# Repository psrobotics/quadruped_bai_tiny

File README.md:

# Quadruped_bai_tiny v1

Still working on detailed document.

## Videos

[Walking](https://youtu.be/wHSh3s8Uc68)  /  [Jumping](https://youtu.be/LqSfARLMR58)  /  [Leg demo](https://www.youtube.com/watch?v=xufyeLivXR8)

## File Structure

* /hardware - CAD design

* /electronic - Motor driver, Main controller brd, Encoder brd, IIC bridge brd

* /sim - V-rep simulation, Kinematics, Dynamics

* /software - Firmware

## Reducer

## Leg Assembly

## Body Assembly

## Motor Driver

## Main Controller

## License
MIT License

## Contact
* Shuang Peng, {shuangpe}@usc.edu

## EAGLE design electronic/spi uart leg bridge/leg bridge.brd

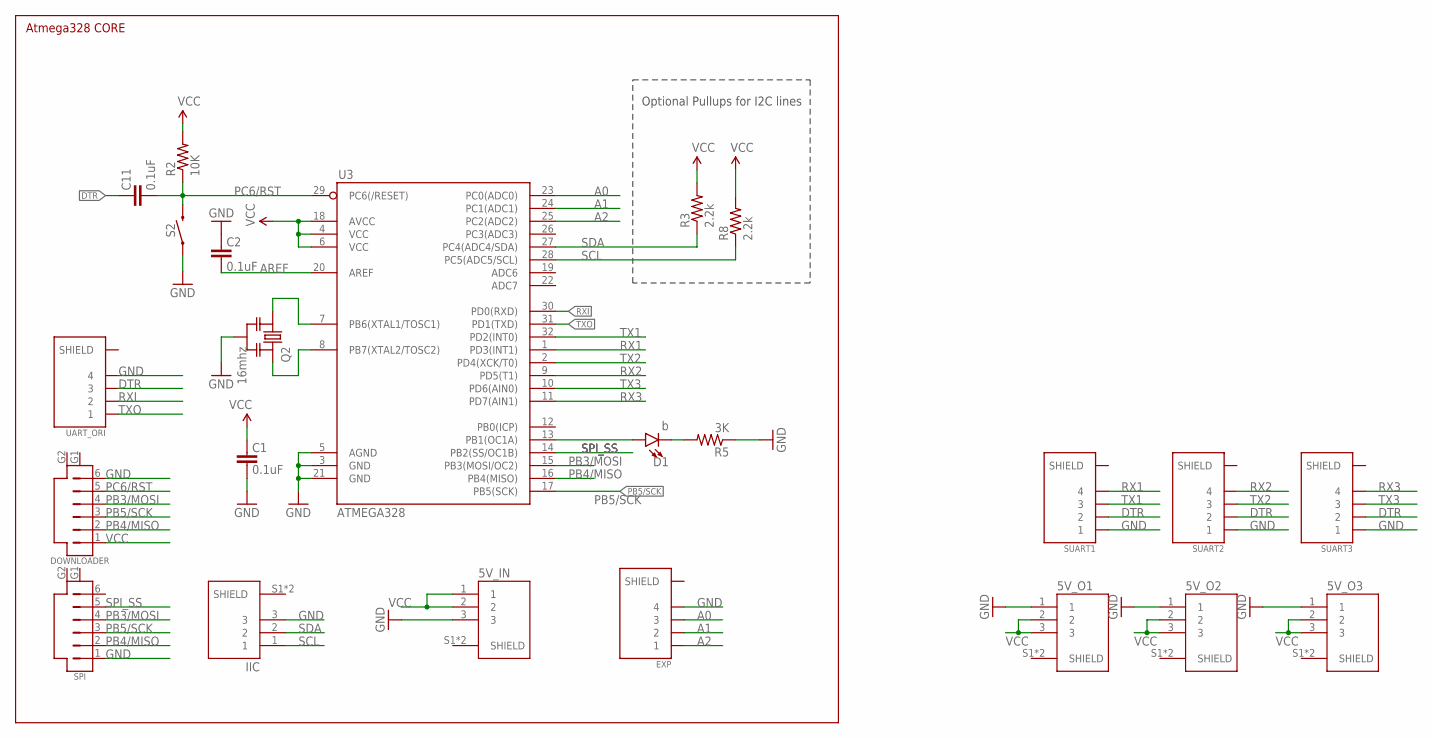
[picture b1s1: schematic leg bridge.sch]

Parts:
5V_IN, 5V_O1, 5V_O2, 5V_O3: SM03B-SRSS-TB(LF)(SN); JST_SM03B-SRSS-TB(LF)(SN)
C1, C2, C11: 0.1uF; 0603-CAP
D1: b; LED-0603
DOWNLOADER: SM06B-SRSS-TB; SM06B
EXP: SM04B-SRSS-TB(LF)(SN); JST_SM04B-SRSS-TB(LF)(SN)
IIC: SM03B-SRSS-TB(LF)(SN); JST_SM03B-SRSS-TB(LF)(SN)
Q2: 16mhz; RESONATOR_MURATA2
R2: 10K; 0603-RES
R3, R8: 2.2k; 0603-RES
R5: 3K; 0603-RES
S2: MOMENTARY-SWITCH-SPST-SMD-RIGHT-ANGLE; TACTILE_SWITCH_SMD_RIGHT_ANGLE
SPI: SM06B-SRSS-TB; SM06B
SUART1, SUART2, SUART3: SM04B-SRSS-TB(LF)(SN); JST_SM04B-SRSS-TB(LF)(SN)
U3: ATMEGA328; TQFP32-08
UART_ORI: SM04B-SRSS-TB(LF)(SN); JST_SM04B-SRSS-TB(LF)(SN)

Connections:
A0: EXP.3, U3.23 (PC0(ADC0))
A1: EXP.2, U3.24 (PC1(ADC1))
A2: EXP.1, U3.25 (PC2(ADC2))
AREF: C2.1, U3.20 (AREF)
DTR: C11.2, SUART1.2, SUART2.2, SUART3.2, UART_ORI.3
GND: 5V_IN.3, 5V_O1.1, 5V_O2.1, 5V_O3.1, C1.1, C2.2, DOWNLOADER.6, EXP.4, IIC.3, Q2.2, R5.1, S2.1, SPI.1, SUART1.1, SUART2.1, SUART3.1, U3.3 (GND), U3.5 (AGND), U3.21 (GND), UART_ORI.4
unnamed: Q2.1, U3.7 (PB6(XTAL1/TOSC1))
unnamed: Q2.3, U3.8 (PB7(XTAL2/TOSC2))
unnamed: D1.A, U3.13 (PB1(OC1A))
unnamed: D1.C, R5.2
PB3/MOSI: DOWNLOADER.4, SPI.4, U3.15 (PB3(MOSI/OC2))
PB4/MISO: DOWNLOADER.2, SPI.2, U3.16 (PB4(MISO))
PB5/SCK: DOWNLOADER.3, SPI.3, U3.17 (PB5(SCK))
PC6/RST: C11.1, DOWNLOADER.5, R2.1, S2.2, U3.29 (PC6(/RESET))
RX1: SUART1.4, U3.1 (PD3(INT1))
RX2: SUART2.4, U3.9 (PD5(T1))
RX3: SUART3.4, U3.11 (PD7(AIN1))
RXI: U3.30 (PD0(RXD)), UART_ORI.2
SCL: IIC.1, R8.1, U3.28 (PC5(ADC5/SCL))
SDA: IIC.2, R3.1, U3.27 (PC4(ADC4/SDA))
SPI_SS: SPI.5, U3.14 (PB2(SS/OC1B))
TX1: SUART1.3, U3.32 (PD2(INT0))
TX2: SUART2.3, U3.2 (PD4(XCK/T0))
TX3: SUART3.3, U3.10 (PD6(AIN0))
TXO: U3.31 (PD1(TXD)), UART_ORI.1
VCC: 5V_IN.1, 5V_IN.2, 5V_O1.2, 5V_O1.3, 5V_O2.2, 5V_O2.3, 5V_O3.2, 5V_O3.3, C1.2, DOWNLOADER.1, R2.2, R3.2, R8.2, U3.4 (VCC), U3.6 (VCC), U3.18 (AVCC)

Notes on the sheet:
Optional Pullups for I2C lines
Atmega328 CORE

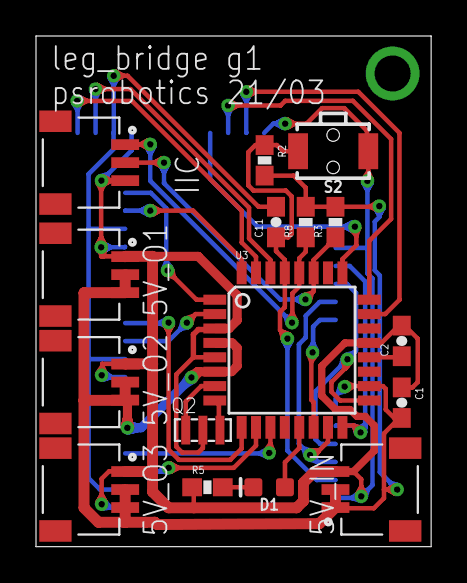
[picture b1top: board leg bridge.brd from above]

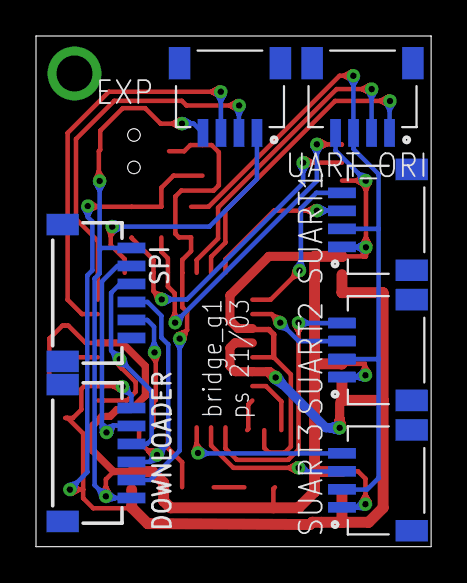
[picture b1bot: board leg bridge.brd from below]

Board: 2 copper layers, 22.0 x 28.4 mm, 23 parts (7 on the bottom side), 26 nets.

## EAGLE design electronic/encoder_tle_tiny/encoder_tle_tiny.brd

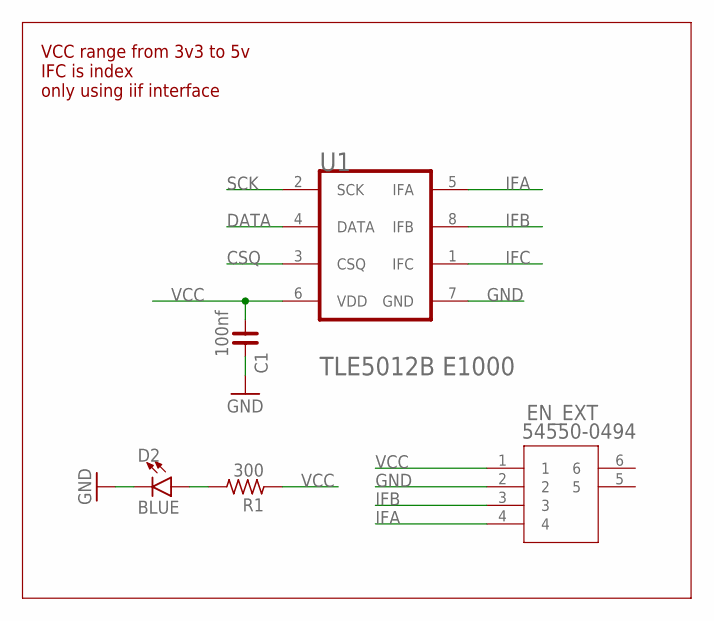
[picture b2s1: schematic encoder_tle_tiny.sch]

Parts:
C1: 100nf; C0603
D2: BLUE; LED-0603
EN_EXT: 54550-0494; CON4_1X4_DRB2_MOL
R1: 300; R0603
U1: INFINEON_TLE5012B_E1000INFINEON_TLE5012B_E1000_0_1; INFINEON_TLE5012B_E1000_1

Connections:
CSQ: U1.3 (CSQ)
DATA: U1.4 (DATA)
GND: C1.2, D2.C, EN_EXT.2, U1.7 (GND)
IFA: EN_EXT.4, U1.5 (IFA)
IFB: EN_EXT.3, U1.8 (IFB)
IFC: U1.1 (IFC)
unnamed: D2.A, R1.2
SCK: U1.2 (SCK)
VCC: C1.1, EN_EXT.1, R1.1, U1.6 (VDD)

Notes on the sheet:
VCC range from 3v3 to 5v IFC is index only using iif interface

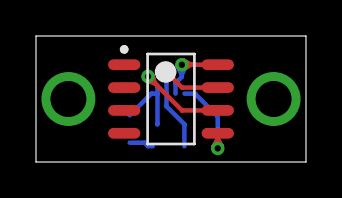
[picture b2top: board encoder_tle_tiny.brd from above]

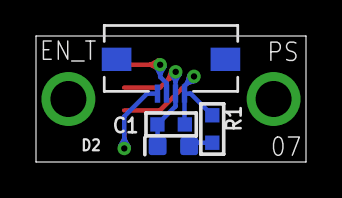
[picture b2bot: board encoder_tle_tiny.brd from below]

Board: 2 copper layers, 15.0 x 7.0 mm, 5 parts (4 on the bottom side), 5 nets.

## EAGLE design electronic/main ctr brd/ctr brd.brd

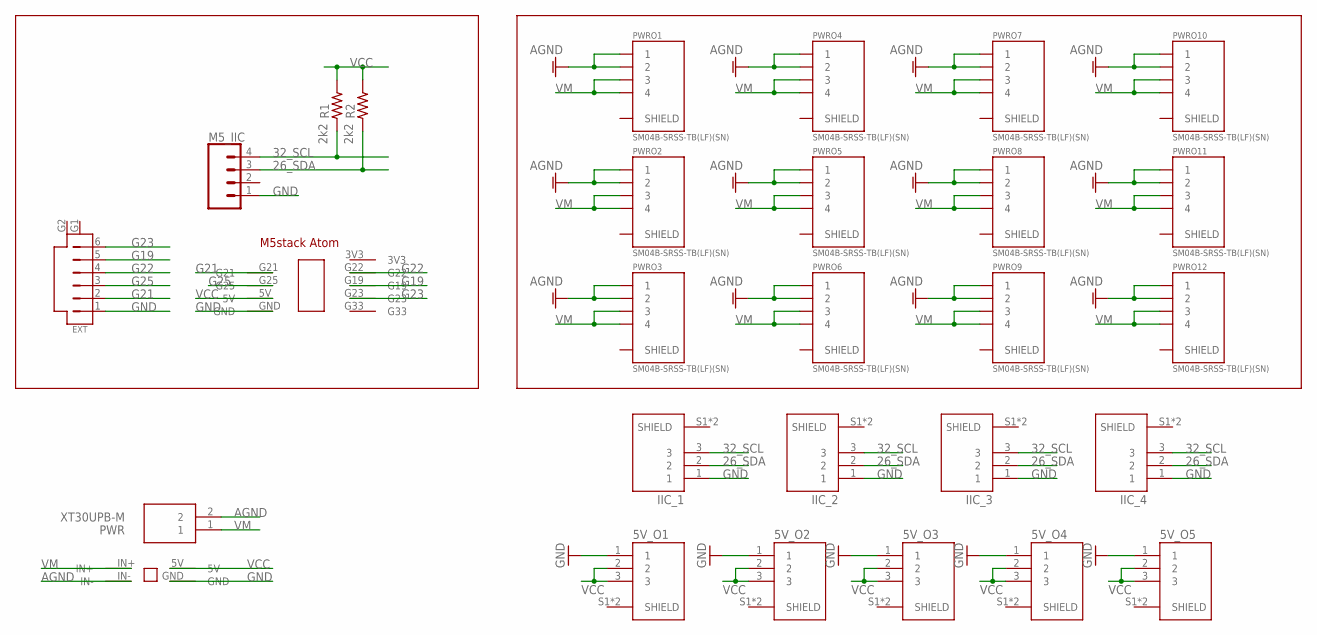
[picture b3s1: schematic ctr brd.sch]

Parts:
5V_O1, 5V_O2, 5V_O3, 5V_O4, 5V_O5: SM03B-SRSS-TB(LF)(SN); JST_SM03B-SRSS-TB(LF)(SN)
EXT: SM06B-SRSS-TB; SM06B
IIC_1, IIC_2, IIC_3, IIC_4: SM03B-SRSS-TB(LF)(SN); JST_SM03B-SRSS-TB(LF)(SN)
M5_IIC: CONN_04JST-PTH; JST-4-PTH
PWR: XT30UPB-M; SHDR2W160P0X500_1X2_1020X520X1
PWRO1, PWRO2, PWRO3, PWRO4, PWRO5, PWRO6, PWRO7, PWRO8, PWRO9, PWRO10, PWRO11, PWRO12: SM04B-SRSS-TB(LF)(SN); JST_SM04B-SRSS-TB(LF)(SN)
R1, R2: 2k2; R0603
U$1: M5STACK_ATOM
U$2: 5V_STAB

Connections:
26_SDA: IIC_1.2, IIC_2.2, IIC_3.2, IIC_4.2, M5_IIC.3, R2.1
32_SCL: IIC_1.3, IIC_2.3, IIC_3.3, IIC_4.3, M5_IIC.4, R1.1
AGND: PWR.2, PWRO1.1, PWRO1.2, PWRO2.1, PWRO2.2, PWRO3.1, PWRO3.2, PWRO4.1, PWRO4.2, PWRO5.1, PWRO5.2, PWRO6.1, PWRO6.2, PWRO7.1, PWRO7.2, PWRO8.1, PWRO8.2, PWRO9.1, PWRO9.2, PWRO10.1, PWRO10.2, PWRO11.1, PWRO11.2, PWRO12.1, PWRO12.2, U$2.IN-
G19: EXT.5, U$1.G19
G21: EXT.2, U$1.G21
G22: EXT.4, U$1.G22
G23: EXT.6, U$1.G23
G25: EXT.3, U$1.G25
GND: 5V_O1.1, 5V_O2.1, 5V_O3.1, 5V_O4.1, 5V_O5.1, EXT.1, IIC_1.1, IIC_2.1, IIC_3.1, IIC_4.1, M5_IIC.1, U$1.GND, U$2.GND
VCC: 5V_O1.2, 5V_O1.3, 5V_O2.2, 5V_O2.3, 5V_O3.2, 5V_O3.3, 5V_O4.2, 5V_O4.3, 5V_O5.2, 5V_O5.3, R1.2, R2.2, U$1.5V, U$2.5V
VM: PWR.1, PWRO1.3, PWRO1.4, PWRO2.3, PWRO2.4, PWRO3.3, PWRO3.4, PWRO4.3, PWRO4.4, PWRO5.3, PWRO5.4, PWRO6.3, PWRO6.4, PWRO7.3, PWRO7.4, PWRO8.3, PWRO8.4, PWRO9.3, PWRO9.4, PWRO10.3, PWRO10.4, PWRO11.3, PWRO11.4, PWRO12.3, PWRO12.4, U$2.IN+

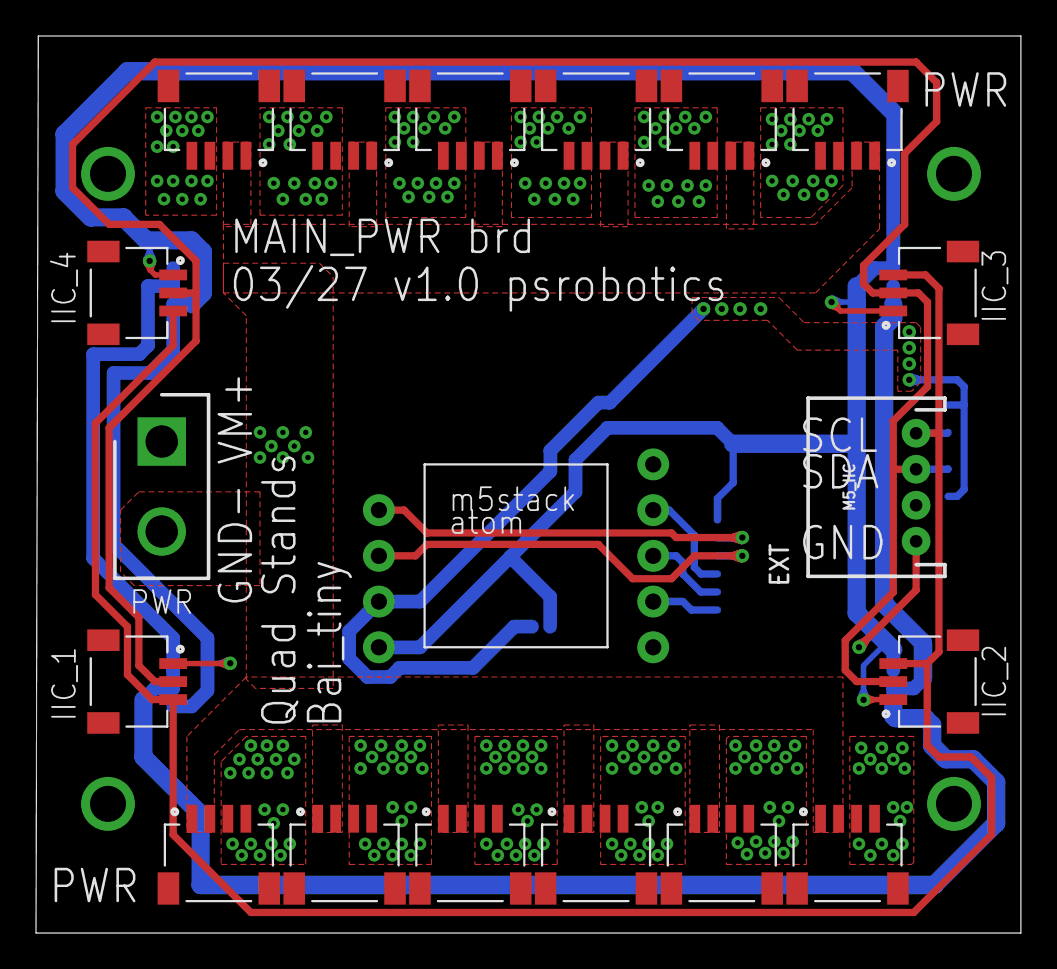
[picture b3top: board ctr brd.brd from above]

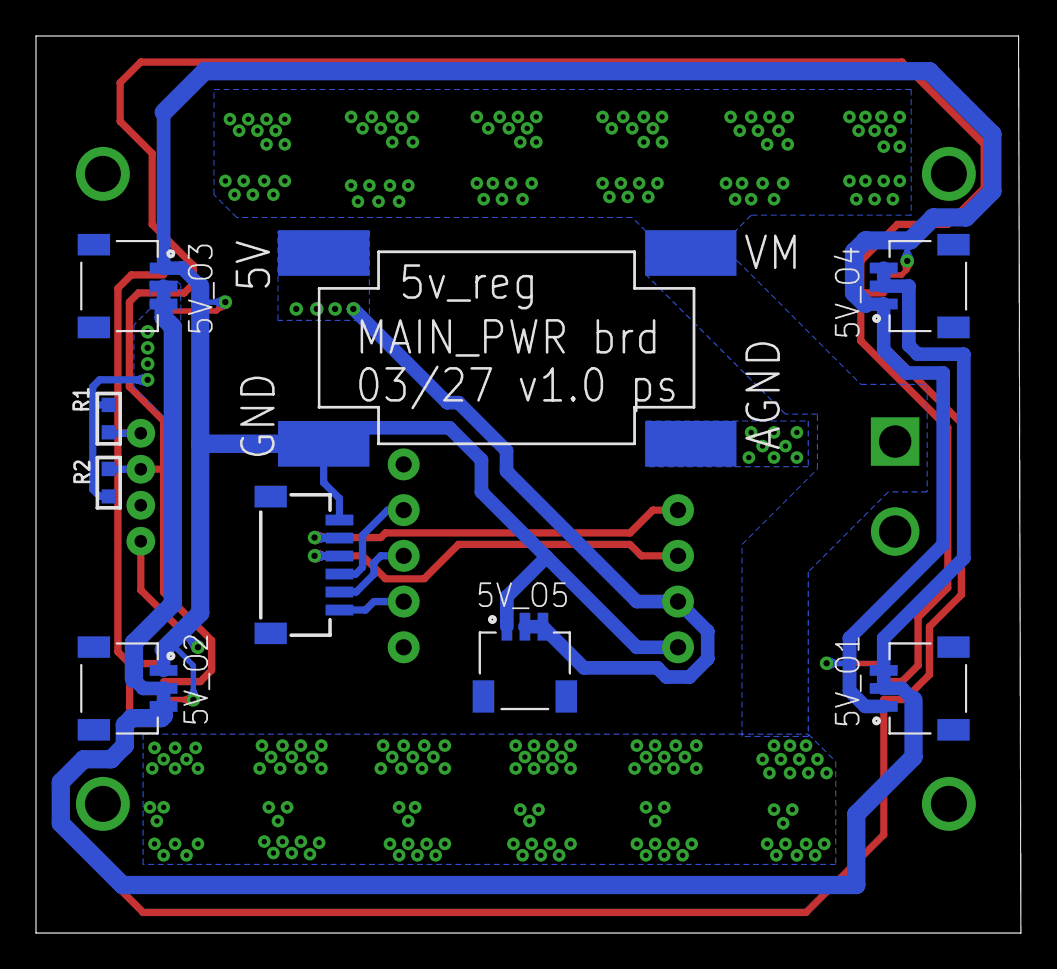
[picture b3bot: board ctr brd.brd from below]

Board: 2 copper layers, 54.7 x 49.8 mm, 28 parts (9 on the bottom side), 11 nets.

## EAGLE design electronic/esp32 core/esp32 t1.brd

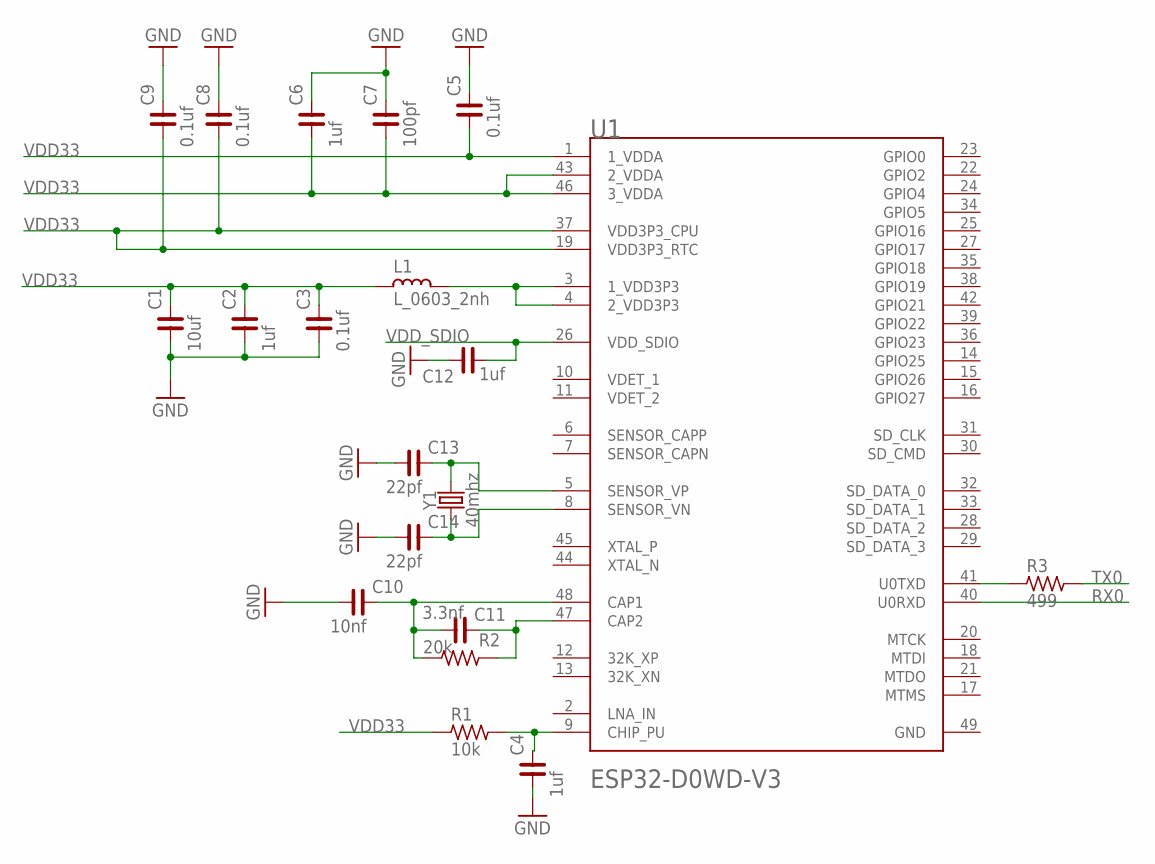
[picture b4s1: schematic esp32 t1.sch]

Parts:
C1: 10uf; C0603
C2, C4, C6, C12: 1uf; C0603
C3, C5, C8, C9: 0.1uf; C0603
C7: 100pf; C0603
C10: 10nf; C0603
C11: 3.3nf; C0603
C13, C14: 22pf; C0603
L1: L_0603_2nh; L0603
R1: 10k; R0603
R2: 20k; R0603
R3: 499; R0603
U1: ESPRESSIF_SYSTEMS_ESP32-D0WD-V3ESPRESSIF_SYSTEMS_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; ESPRESSIF_SYSTEMS_ESP32-D0WD-V3_0
Y1: 40mhz; CRYSTAL-SMD-3.2X1.5MM

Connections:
GND: C1.1, C2.1, C3.1, C4.1, C5.2, C6.2, C7.2, C8.2, C9.2, C10.1, C12.2, C13.1, C14.1, U1.49 (GND)
unnamed: C4.2, R1.2, U1.9 (CHIP_PU)
unnamed: L1.1, U1.3 (1_VDD3P3), U1.4 (2_VDD3P3)
unnamed: C10.2, C11.1, R2.1, U1.48 (CAP1)
unnamed: C11.2, R2.2, U1.47 (CAP2)
unnamed: C13.2, U1.5 (SENSOR_VP), Y1.P$2 (2)
unnamed: R3.1, U1.41 (U0TXD)
unnamed: C14.2, U1.8 (SENSOR_VN), Y1.P$1 (1)
RX0: U1.40 (U0RXD)
TX0: R3.2
VDD33: C1.2, C2.2, C3.2, C5.1, C6.1, C7.1, C8.1, C9.1, L1.2, R1.1, U1.1 (1_VDDA), U1.19 (VDD3P3_RTC), U1.37 (VDD3P3_CPU), U1.43 (2_VDDA), U1.46 (3_VDDA)
VDD_SDIO: C12.1, U1.26 (VDD_SDIO)
VDET_1: U1.10 (VDET_1)
VDET_2: U1.11 (VDET_2)

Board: 2 copper layers, 20 parts (0 on the bottom side), 10 nets, no tracks yet.

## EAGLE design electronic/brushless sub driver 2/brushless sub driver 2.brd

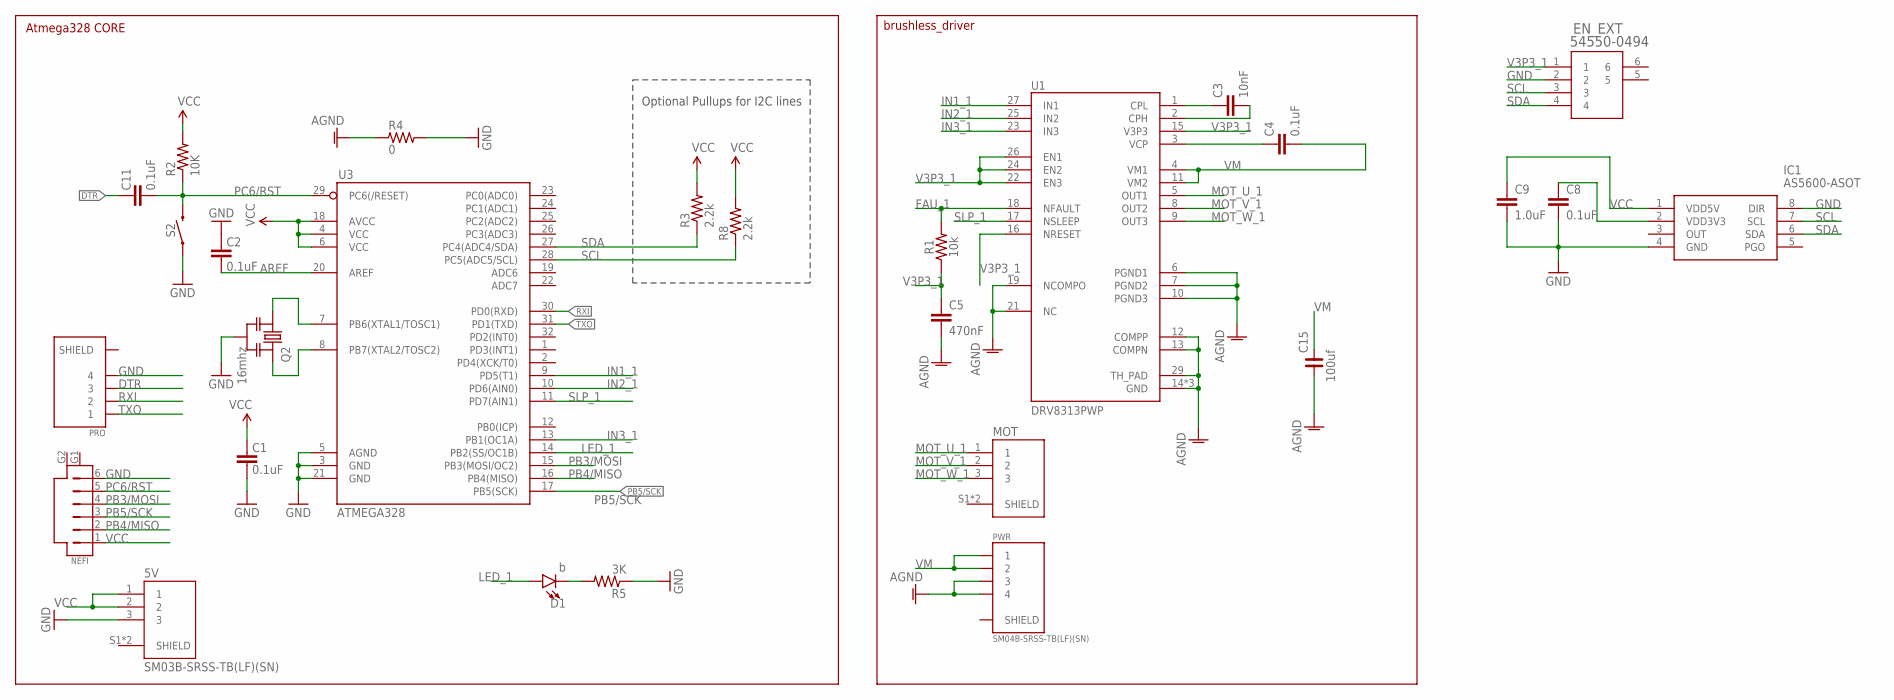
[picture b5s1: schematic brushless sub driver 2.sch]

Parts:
5V: SM03B-SRSS-TB(LF)(SN); JST_SM03B-SRSS-TB(LF)(SN)
C1, C2, C11: 0.1uF; 0603-CAP
C3: 10nF; 0603
C4: 0.1uF; 0603
C5: 470nF; 0603
C8: 0.1uF; 0402
C9: 1.0uF; 0402
C15: 100uf; C1206
D1: b; LED-0603
EN_EXT: 54550-0494; CON4_1X4_DRB2_MOL
IC1: AS5600-ASOT; SOIC127P600X175-8N
MOT: SM03B-SRSS-TB(LF)(SN); JST_SM03B-SRSS-TB(LF)(SN)
NEFI: SM06B-SRSS-TB; SM06B
PRO: SM04B-SRSS-TB(LF)(SN); JST_SM04B-SRSS-TB(LF)(SN)
PWR: SM04B-SRSS-TB(LF)(SN); JST_SM04B-SRSS-TB(LF)(SN)
Q2: 16mhz; RESONATOR_MURATA2
R1: 10k; 0603
R2: 10K; 0603-RES
R3, R8: 2.2k; 0603-RES
R4: 0; R0603
R5: 3K; 0603-RES
S2: MOMENTARY-SWITCH-SPST-SMD-RIGHT-ANGLE; TACTILE_SWITCH_SMD_RIGHT_ANGLE
U1: DRV8313PWP; SOP28P65_970X640X120L60X24T483X275N
U3: ATMEGA328; TQFP32-08

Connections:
AGND: C5.2, C15.1, PWR.3, PWR.4, R4.1, U1.6 (PGND1), U1.7 (PGND2), U1.10 (PGND3), U1.12 (COMPP), U1.13 (COMPN), U1.14 (GND), U1.19 (NCOMPO), U1.20 (GND), U1.21 (NC), U1.28 (GND), U1.29 (TH_PAD)
AREF: C2.1, U3.20 (AREF)
DTR: C11.2, PRO.3
FAU_1: R1.2, U1.18 (NFAULT)
GND: 5V.3, C1.1, C2.2, C8.2, C9.2, EN_EXT.2, IC1.4 (GND), IC1.8 (DIR), NEFI.6, PRO.4, Q2.2, R4.2, R5.1, S2.1, U3.3 (GND), U3.5 (AGND), U3.21 (GND)
IN1_1: U1.27 (IN1), U3.9 (PD5(T1))
IN2_1: U1.25 (IN2), U3.10 (PD6(AIN0))
IN3_1: U1.23 (IN3), U3.13 (PB1(OC1A))
LED_1: D1.A, U3.14 (PB2(SS/OC1B))
MOT_U_1: MOT.1, U1.5 (OUT1)
MOT_V_1: MOT.2, U1.8 (OUT2)
MOT_W_1: MOT.3, U1.9 (OUT3)
unnamed: Q2.1, U3.7 (PB6(XTAL1/TOSC1))
unnamed: Q2.3, U3.8 (PB7(XTAL2/TOSC2))
unnamed: C3.1, U1.1 (CPL)
unnamed: C3.2, U1.2 (CPH)
unnamed: C4.1, U1.3 (VCP)
unnamed: C8.1, IC1.2 (VDD3V3)
unnamed: D1.C, R5.2
PB3/MOSI: NEFI.4, U3.15 (PB3(MOSI/OC2))
PB4/MISO: NEFI.2, U3.16 (PB4(MISO))
PB5/SCK: NEFI.3, U3.17 (PB5(SCK))
PC6/RST: C11.1, NEFI.5, R2.1, S2.2, U3.29 (PC6(/RESET))
RXI: PRO.2, U3.30 (PD0(RXD))
SCL: EN_EXT.3, IC1.7 (SCL), R8.1, U3.28 (PC5(ADC5/SCL))
SDA: EN_EXT.4, IC1.6 (SDA), R3.1, U3.27 (PC4(ADC4/SDA))
SLP_1: U1.17 (NSLEEP), U3.11 (PD7(AIN1))
TXO: PRO.1, U3.31 (PD1(TXD))
V3P3_1: C5.1, EN_EXT.1, R1.1, U1.15 (V3P3), U1.16 (NRESET), U1.22 (EN3), U1.24 (EN2), U1.26 (EN1)
VCC: 5V.1, 5V.2, C1.2, C9.1, IC1.1 (VDD5V), NEFI.1, R2.2, R3.2, R8.2, U3.4 (VCC), U3.6 (VCC), U3.18 (AVCC)
VM: C4.2, C15.2, PWR.1, PWR.2, U1.4 (VM1), U1.11 (VM2)

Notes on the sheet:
Optional Pullups for I2C lines
Atmega328 CORE
brushless_driver

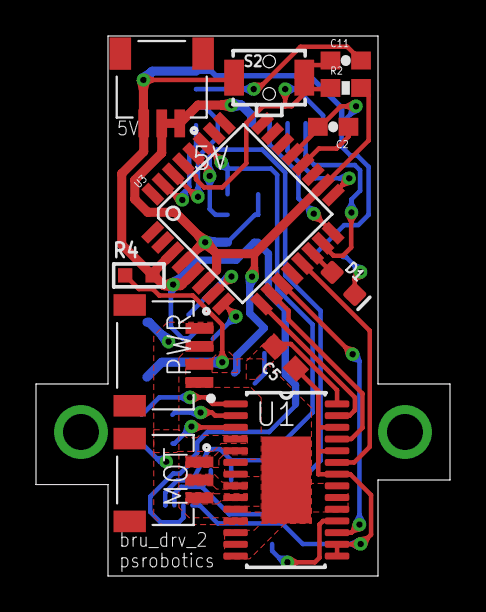
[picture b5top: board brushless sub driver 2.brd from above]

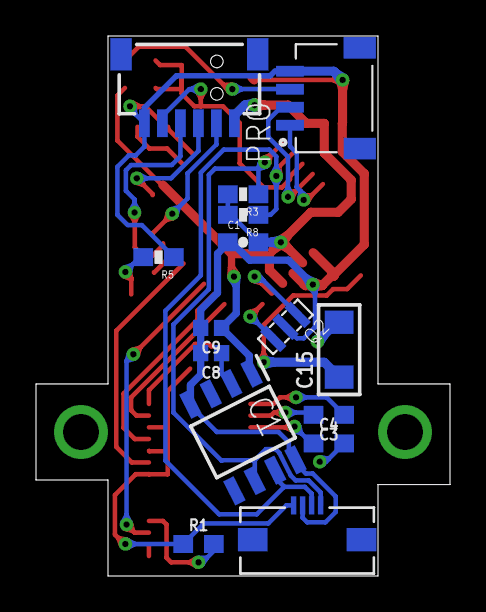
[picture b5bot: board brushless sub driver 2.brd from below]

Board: 2 copper layers, 23.0 x 30.0 mm, 27 parts (15 on the bottom side), 31 nets.

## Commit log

2022-01-23 add: 0123
2022-02-07 add: video
2023-10-22 add: 1021 open docu
2023-10-22 add: 1021
2023-10-22 add: 1022 clean gcode

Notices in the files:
parts and their libraries:
SparkFun-Capacitors: Licensing: Creative Commons ShareAlike 4.0 International - https://creativecommons.org/licenses/by-sa/4.0
rc-master-smd: Copyright (C) 2007, Bob Starr
m-pad-2.1: License : GNU General Public License version 2 (see bottom)
